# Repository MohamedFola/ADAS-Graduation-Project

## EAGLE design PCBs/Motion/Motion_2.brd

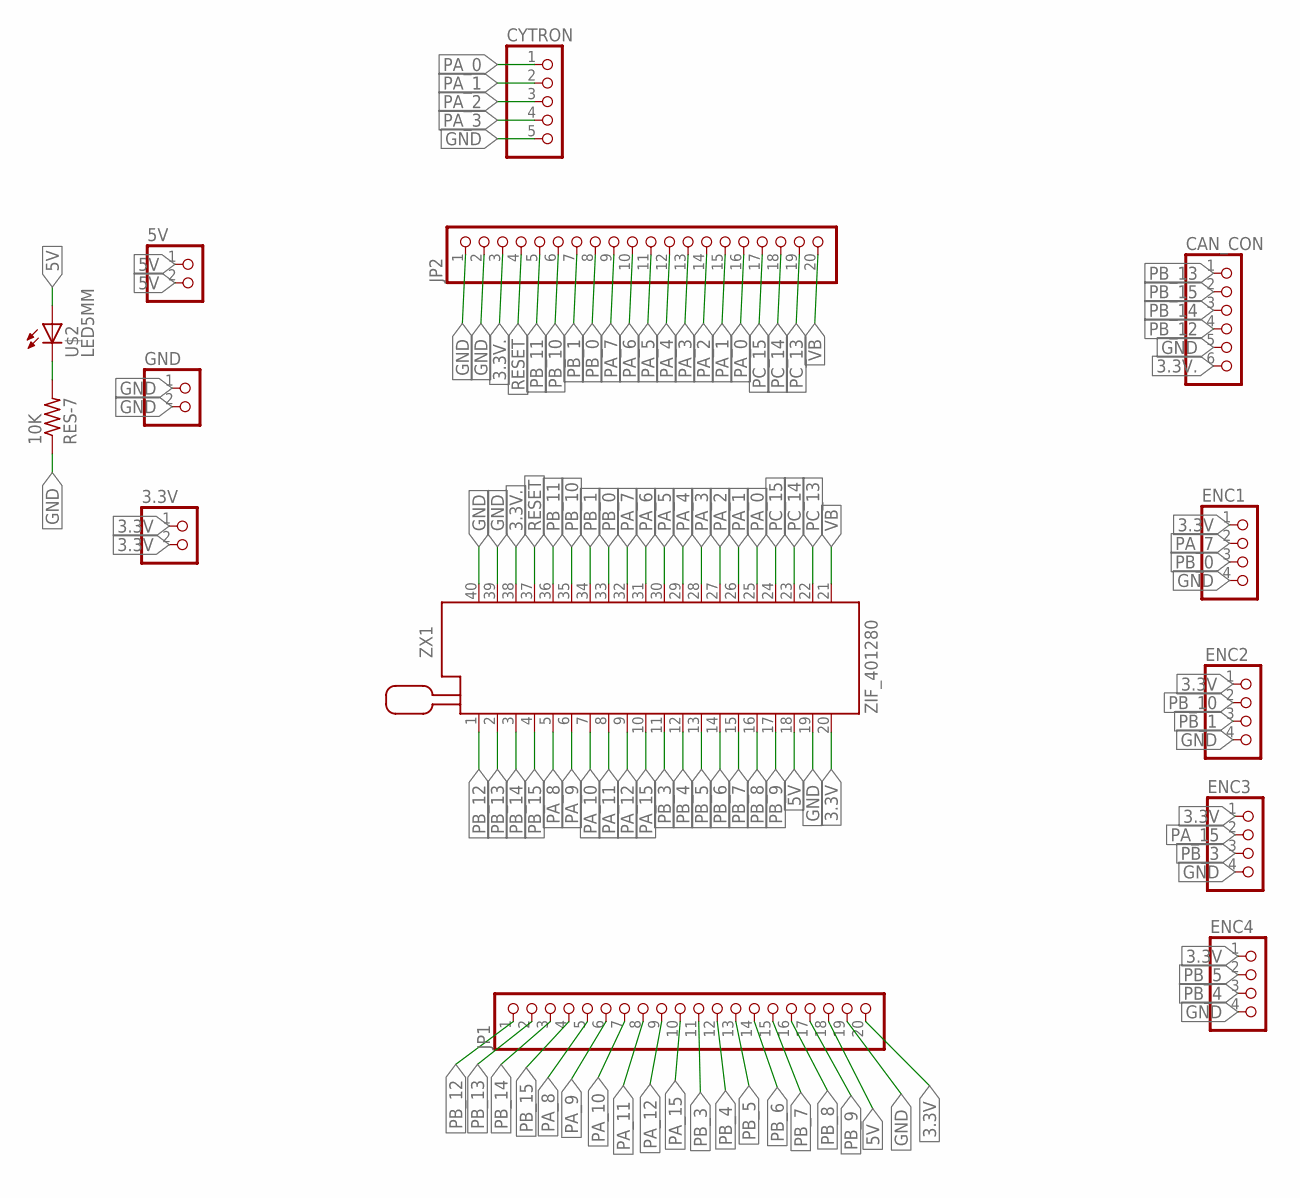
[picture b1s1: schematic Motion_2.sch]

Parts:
3.3V, 5V: PINHD-2_DATA; 1X02_DATA
10K: RES-7; 0204/7
CAN_CON: PINHD-6_DATA; 1X06_DATA
CYTRON: PINHD-5_DATA; 1X05_DATA
ENC1, ENC2, ENC3, ENC4: PINHD-4_DATA; 1X04_DATA
GND: PINHD-2_DATA; 1X02_DATA
JP1, JP2: PINHD-1X20; 1X20
U$2: LED5MM
ZX1: ZIF_401280; 240-1280-00-0602J

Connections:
3.3V: 3.3V.1, 3.3V.2, ENC1.1, ENC2.1, ENC3.1, ENC4.1, JP1.20, ZX1.20
3.3V.: CAN_CON.6, JP2.3, ZX1.38
5V: 5V.1, 5V.2, JP1.18, U$2.A, ZX1.18
GND: 10K.1, CAN_CON.5, CYTRON.5, ENC1.4, ENC2.4, ENC3.4, ENC4.4, GND.1, GND.2, JP1.19, JP2.1, JP2.2, ZX1.19, ZX1.39, ZX1.40
unnamed: 10K.2, U$2.K (C)
PA_0: CYTRON.1, JP2.16, ZX1.25
PA_1: CYTRON.2, JP2.15, ZX1.26
PA_2: CYTRON.3, JP2.14, ZX1.27
PA_3: CYTRON.4, JP2.13, ZX1.28
PA_4: JP2.12, ZX1.29
PA_5: JP2.11, ZX1.30
PA_6: JP2.10, ZX1.31
PA_7: ENC1.2, JP2.9, ZX1.32
PA_8: JP1.5, ZX1.5
PA_9: JP1.6, ZX1.6
PA_10: JP1.7, ZX1.7
PA_11: JP1.8, ZX1.8
PA_12: JP1.9, ZX1.9
PA_15: ENC3.2, JP1.10, ZX1.10
PB_0: ENC1.3, JP2.8, ZX1.33
PB_1: ENC2.3, JP2.7, ZX1.34
PB_3: ENC3.3, JP1.11, ZX1.11
PB_4: ENC4.3, JP1.12, ZX1.12
PB_5: ENC4.2, JP1.13, ZX1.13
PB_6: JP1.14, ZX1.14
PB_7: JP1.15, ZX1.15
PB_8: JP1.16, ZX1.16
PB_9: JP1.17, ZX1.17
PB_10: ENC2.2, JP2.6, ZX1.35
PB_11: JP2.5, ZX1.36
PB_12: CAN_CON.4, JP1.1, ZX1.1
PB_13: CAN_CON.1, JP1.2, ZX1.2
PB_14: CAN_CON.3, JP1.3, ZX1.3
PB_15: CAN_CON.2, JP1.4, ZX1.4
PC_13: JP2.19, ZX1.22
PC_14: JP2.18, ZX1.23
PC_15: JP2.17, ZX1.24
RESET: JP2.4, ZX1.37
VB: JP2.20, ZX1.21

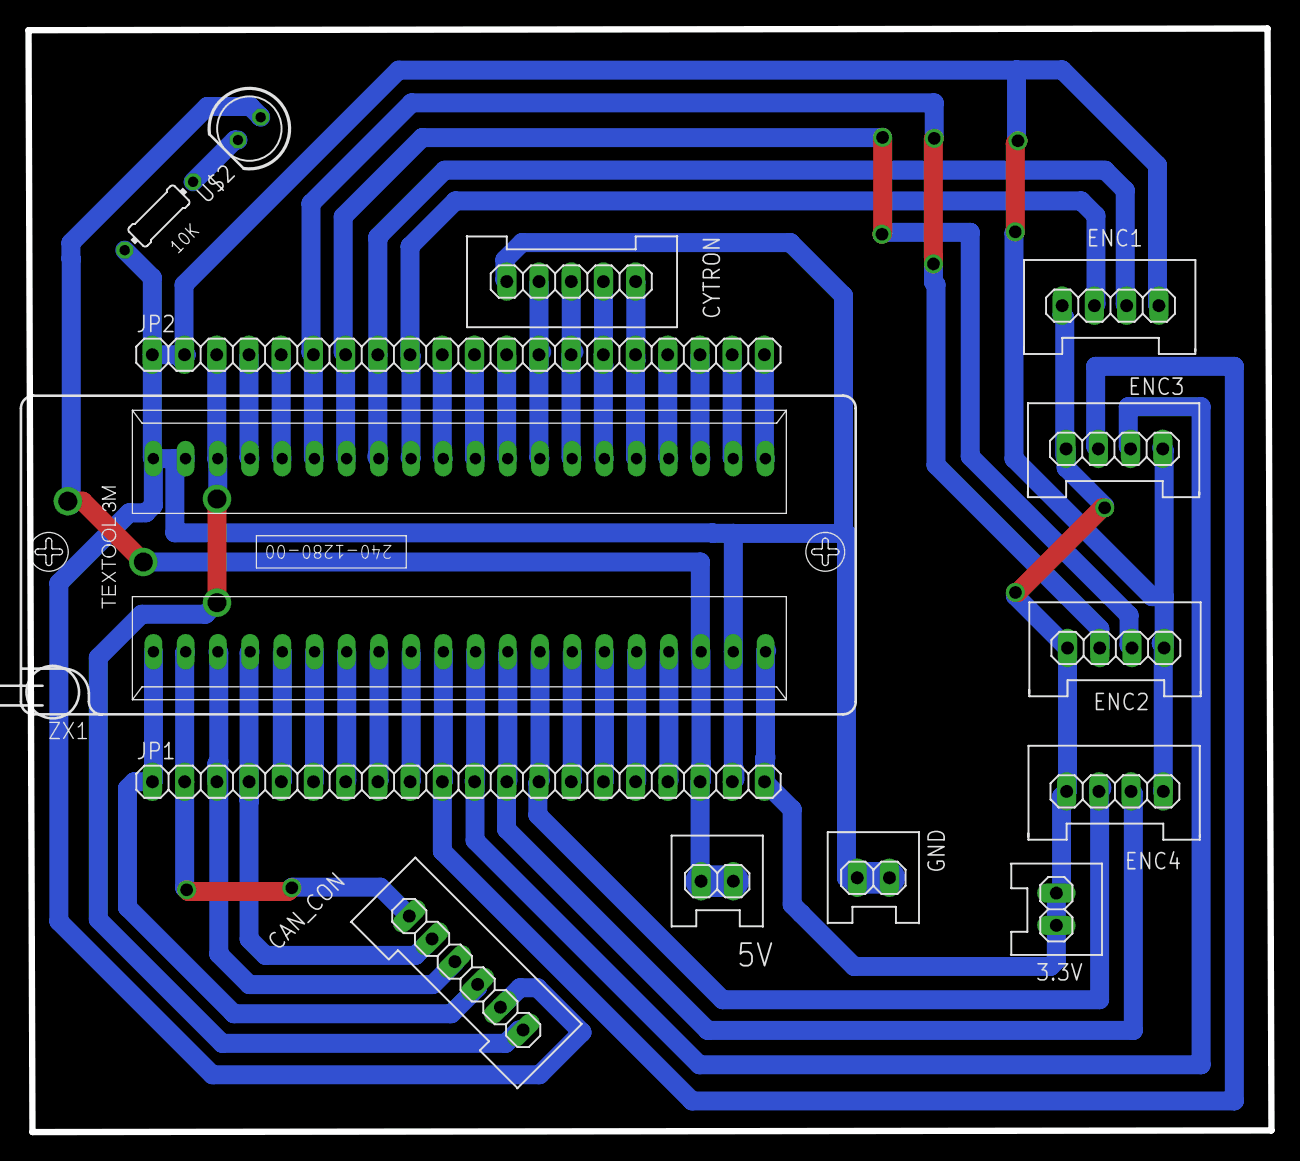
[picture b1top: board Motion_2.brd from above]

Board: 2 copper layers, 98.0 x 87.0 mm, 14 parts (0 on the bottom side), 39 nets.

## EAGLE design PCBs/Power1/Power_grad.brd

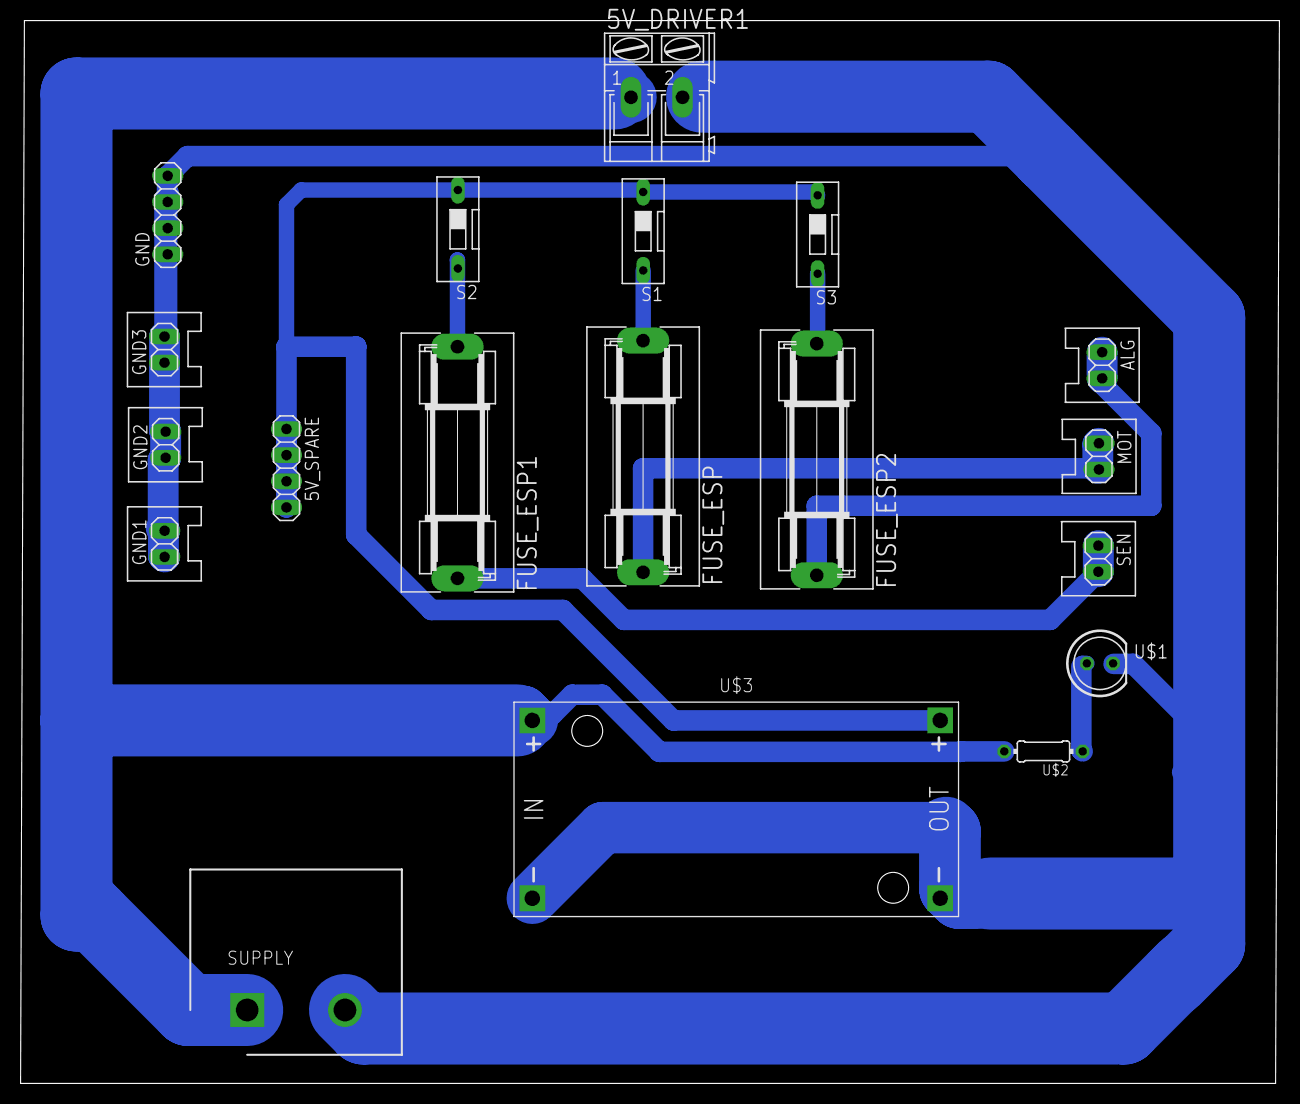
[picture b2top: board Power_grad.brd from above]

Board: 2 copper layers, 122.3 x 103.2 mm, 19 parts (0 on the bottom side), 10 nets.

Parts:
5V_DRIVER1: AK300/2
5V_SPARE: 1X04
ALG: 1X02_DATA
FUSE_ESP, FUSE_ESP1, FUSE_ESP2: SH22,5A
GND: 1X04
GND1, GND2, GND3: 1X02_DATA
MOT: 1X02_DATA
S1, S2, S3: DS-01
SEN: 1X02_DATA
SUPPLY: HB9500-9.5-2P; SHDR2W140P0X950_1X2_2055X1800X
U$1: LED5MM
U$2: RES-7; 0204/7
U$3: DC-DC-STEP-DOWN-LM2596

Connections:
5V: 5V_SPARE.1, 5V_SPARE.2, 5V_SPARE.3, 5V_SPARE.4, S1.1, S2.1, S3.1, U$3.OUT+
12V: 5V_DRIVER1.1, SUPPLY.1, U$2.2, U$3.IN+
ALG: ALG.1, ALG.2, FUSE_ESP2.1
GND: 5V_DRIVER1.2, GND.1, GND.2, GND.3, GND.4, GND1.1, GND1.2, GND2.1, GND2.2, GND3.1, GND3.2, SUPPLY.2, U$1.K, U$3.IN-, U$3.OUT-
MOT: FUSE_ESP.1, MOT.1, MOT.2
unnamed: U$1.A, U$2.1
unnamed: FUSE_ESP1.2, S2.2
unnamed: FUSE_ESP.2, S1.2
unnamed: FUSE_ESP2.2, S3.2
SEN: FUSE_ESP1.1, SEN.1, SEN.2

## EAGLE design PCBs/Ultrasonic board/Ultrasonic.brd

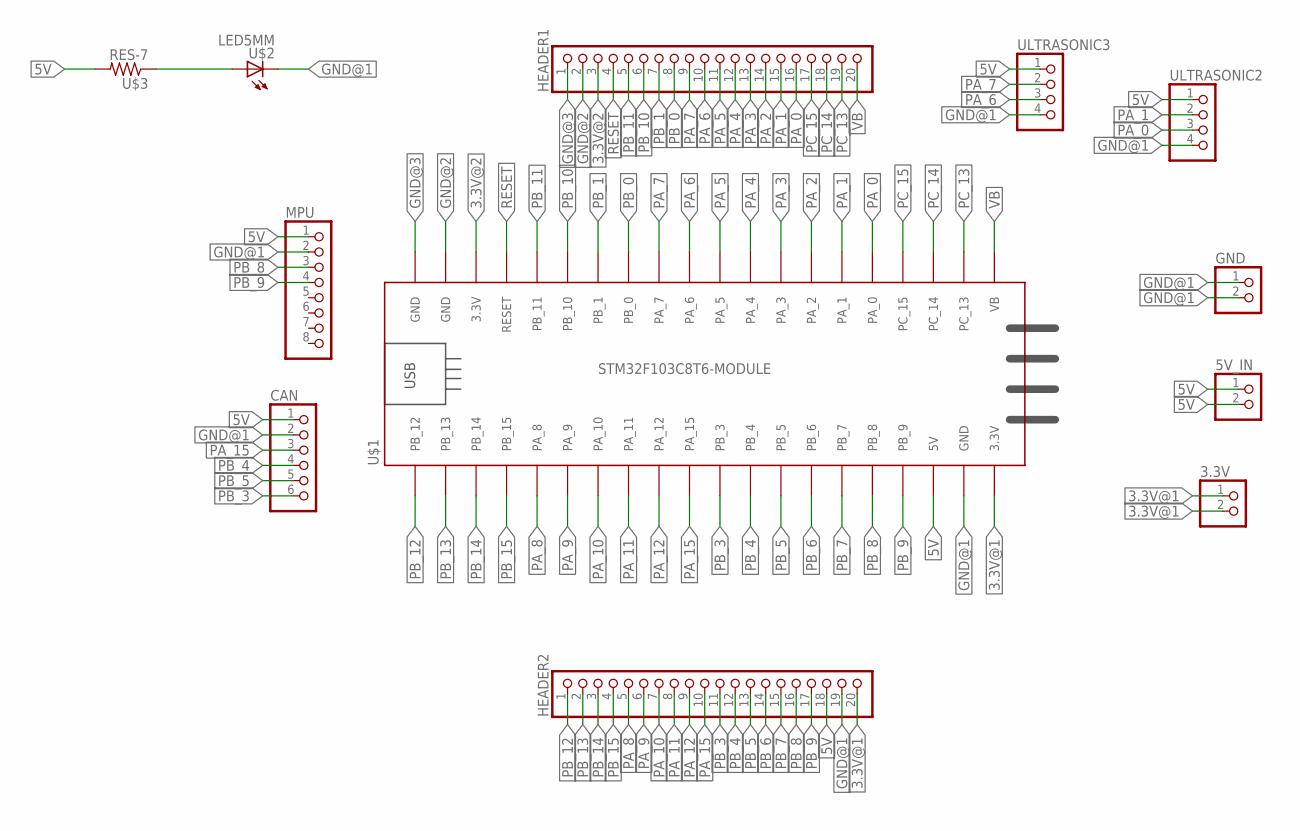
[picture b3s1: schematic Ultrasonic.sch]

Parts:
3.3V, 5V_IN: PINHD-2_DATA; 1X02_DATA
CAN: PINHD-6_DATA; 1X06_DATA
GND: PINHD-2_DATA; 1X02_DATA
HEADER1, HEADER2: PINHD-1X20; 1X20
MPU: PINHD-1X8; 1X08
U$1: STM32F103C8T6-MODULE
U$2: LED5MM
U$3: RES-7; 0204/7
ULTRASONIC2, ULTRASONIC3: PINHD-4_DATA; 1X04_DATA

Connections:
3.3V@1: 3.3V.1, 3.3V.2, HEADER2.20, U$1.3.3V_1 (3.3V)
3.3V@2: HEADER1.3, U$1.3.3V_2 (3.3V)
5V: 5V_IN.1, 5V_IN.2, CAN.1, HEADER2.18, MPU.1, U$1.5V, U$3.2, ULTRASONIC2.1, ULTRASONIC3.1
GND@1: CAN.2, GND.1, GND.2, HEADER2.19, MPU.2, U$1.GND_1 (GND), U$2.K (C), ULTRASONIC2.4, ULTRASONIC3.4
GND@2: HEADER1.2, U$1.GND_2 (GND)
GND@3: HEADER1.1, U$1.GND_3 (GND)
unnamed: U$2.A, U$3.1
PA_0: HEADER1.16, U$1.PA_0, ULTRASONIC2.3
PA_1: HEADER1.15, U$1.PA_1, ULTRASONIC2.2
PA_2: HEADER1.14, U$1.PA_2
PA_3: HEADER1.13, U$1.PA_3
PA_4: HEADER1.12, U$1.PA_4
PA_5: HEADER1.11, U$1.PA_5
PA_6: HEADER1.10, U$1.PA_6, ULTRASONIC3.3
PA_7: HEADER1.9, U$1.PA_7, ULTRASONIC3.2
PA_8: HEADER2.5, U$1.PA_8
PA_9: HEADER2.6, U$1.PA_9
PA_10: HEADER2.7, U$1.PA_10
PA_11: HEADER2.8, U$1.PA_11
PA_12: HEADER2.9, U$1.PA_12
PA_15: CAN.3, HEADER2.10, U$1.PA_15
PB_0: HEADER1.8, U$1.PB_0
PB_1: HEADER1.7, U$1.PB_1
PB_3: CAN.6, HEADER2.11, U$1.PB_3
PB_4: CAN.4, HEADER2.12, U$1.PB_4
PB_5: CAN.5, HEADER2.13, U$1.PB_5
PB_6: HEADER2.14, U$1.PB_6
PB_7: HEADER2.15, U$1.PB_7
PB_8: HEADER2.16, MPU.3, U$1.PB_8
PB_9: HEADER2.17, MPU.4, U$1.PB_9
PB_10: HEADER1.6, U$1.PB_10
PB_11: HEADER1.5, U$1.PB_11
PB_12: HEADER2.1, U$1.PB_12
PB_13: HEADER2.2, U$1.PB_13
PB_14: HEADER2.3, U$1.PB_14
PB_15: HEADER2.4, U$1.PB_15
PC_13: HEADER1.19, U$1.PC_13
PC_14: HEADER1.18, U$1.PC_14
PC_15: HEADER1.17, U$1.PC_15
RESET: HEADER1.4, U$1.RESET
VB: HEADER1.20, U$1.VB

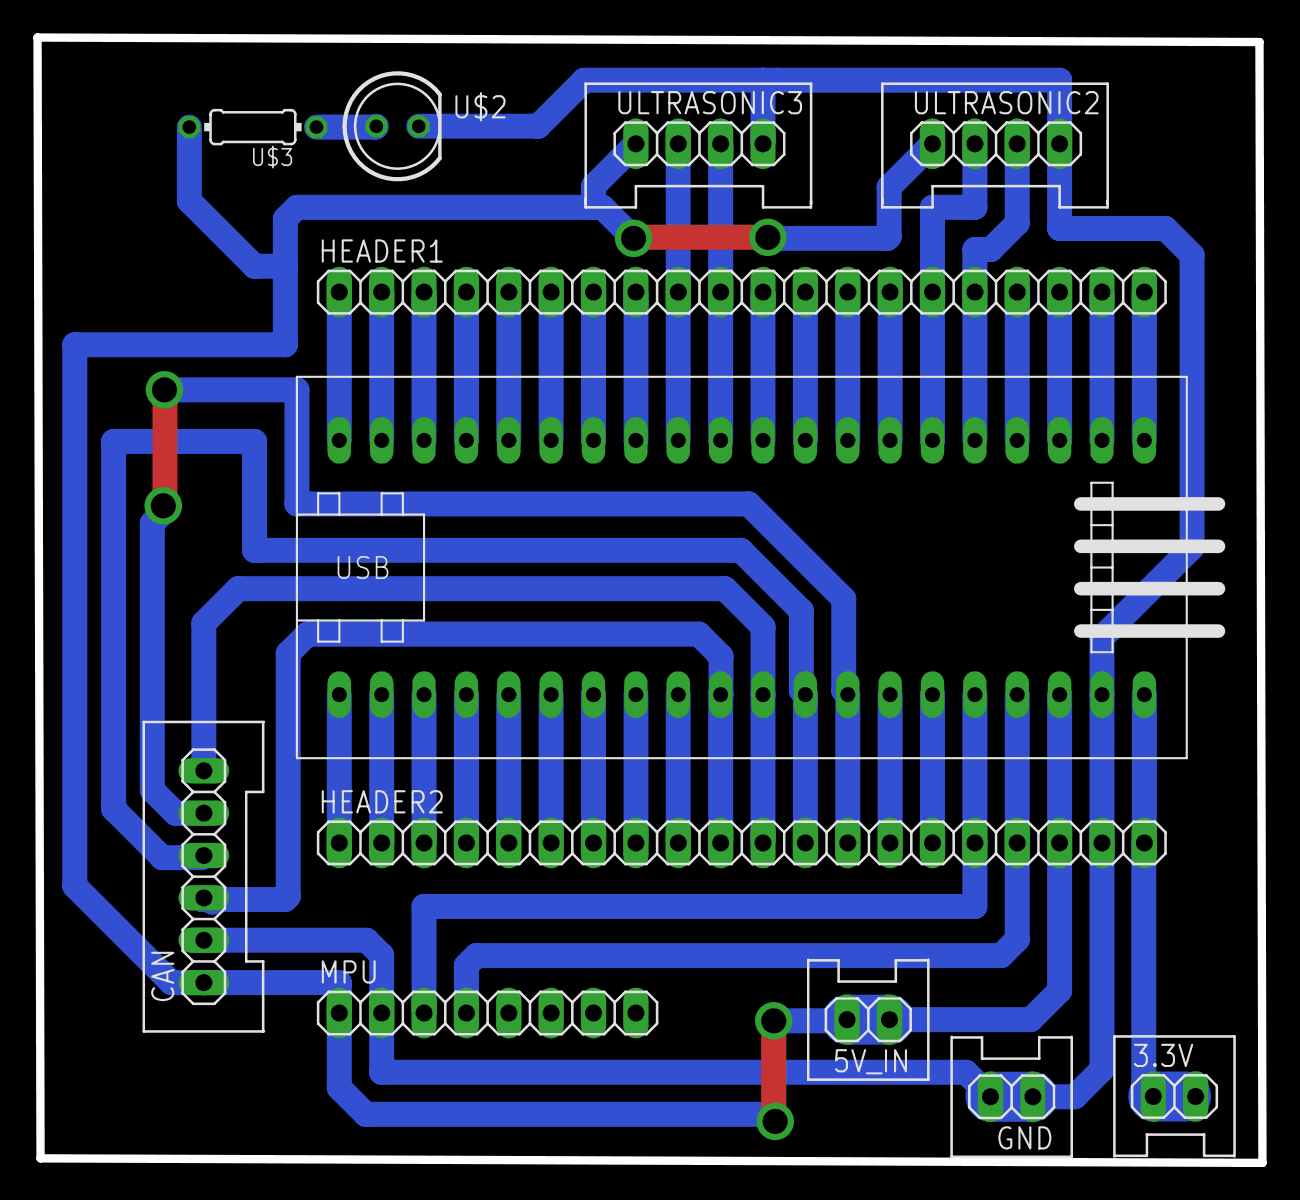
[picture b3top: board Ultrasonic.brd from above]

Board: 2 copper layers, 73.4 x 67.5 mm, 12 parts (0 on the bottom side), 41 nets.

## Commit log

2022-12-28 Create ARM_Drivers
2022-12-30 Add files via upload
    First Commit for ARM Drivers --> BIT_MATH.h & STD_TYPES.h & Software_Delay.c & Software_Delay.h
2022-12-30 First Commit For ARM Drivers
    Included files: Bit manipulation header file & Standard types header files & Software delay Driver
2022-12-30 First Commit for ARM drivers
    Included files are BIT_MATH.h, STD_TYPES.h, Software_Delay.h and Software_Delay.c
2022-12-30 READ ME!!!!!
2022-12-30 References for Cortex M3 -> STM32F10xx
    Programming Manual, Register Description, and Technical Reference Manual
2023-01-02 Fixing Pins numbering
2023-01-31 PORT Driver first commit -- Mohamed Hassan
2023-02-01 Create 02-DIO
    DIO v1
2023-02-01 Add files via upload
    DIO v1
2023-02-01 Systick v1.0 by Mohab and Bassiony
2023-02-01 RCC v1.0 by Magdy and Yasser
2023-02-02 Fixing some bugs
2023-02-02 Adding Peripherals IDs
2023-02-02 Modified RCC program and fixed some errors
2023-02-04 Adding our Proposal
2023-02-07 I2C Driver first commit by Fola
2023-02-09 Adding NVIC Driver
2023-02-09 Adding EXTI Driver
2023-02-09 Adding AFIO Driver
2023-02-10 Add files via upload
    TIMER WORKING BUT SET PERIODIC AND SINGLE INTERVAL NEEDS TO BE REVISED
2023-02-11 Changing interface file
2023-02-12 Fixed the single and periodic interval function
2023-02-12 Adding Comments and return Error status
2023-02-15 Fixing Bugs
2023-02-15 Improving Driver
2023-02-15 Adding Feature
2023-02-17 SPI Driver implementation by Fola
2023-02-17 adding some IMOPRTANT notes for spi driver
2023-02-17 PWM v1 tested
2023-02-18 Some modifications and documentation work
2023-02-26 Adding ISRs for more EXTIs
2023-03-03 Fixing Bug
2023-03-03 Editting LIB paths
2023-03-03 Encoder implementation v1
2023-03-03 Encoder v1
2023-03-07 Adding ICU and TIM4
2023-03-07 Adding PWM4
2023-03-08 Motion board v1
2023-03-09 Ultrasonic ready to work but there is fluctiations
2023-03-11 Adding Initializations and Configurations functions
2023-03-12 Added Ultrasonic & Power PCBs
2023-03-20 Motor driver need to be tested
2023-03-22 fixing bugs and testing I2C and SPI
2023-04-10 Motor motion driver
2023-04-12 Power modify
2023-04-12 adding init files and fixing some bugs
2023-04-24 PID v1.0
2023-04-24 PID v1
2023-04-28 MCP v1
2023-05-03 SPI fixing bugs and adding test project
2023-05-03 adding pm and rm
2023-05-05 UART v1
2023-05-05 UART v1.0
2023-05-05 USART modify
2023-05-09 Updating Ultrasonic
2023-05-19 Updating drivers
2023-05-21 Added comm handler driver
2023-05-24 CommHandler and some drivers Update
2023-06-30 adding boards codes
2023-07-06 adding a zip file that contains all codes of the board
